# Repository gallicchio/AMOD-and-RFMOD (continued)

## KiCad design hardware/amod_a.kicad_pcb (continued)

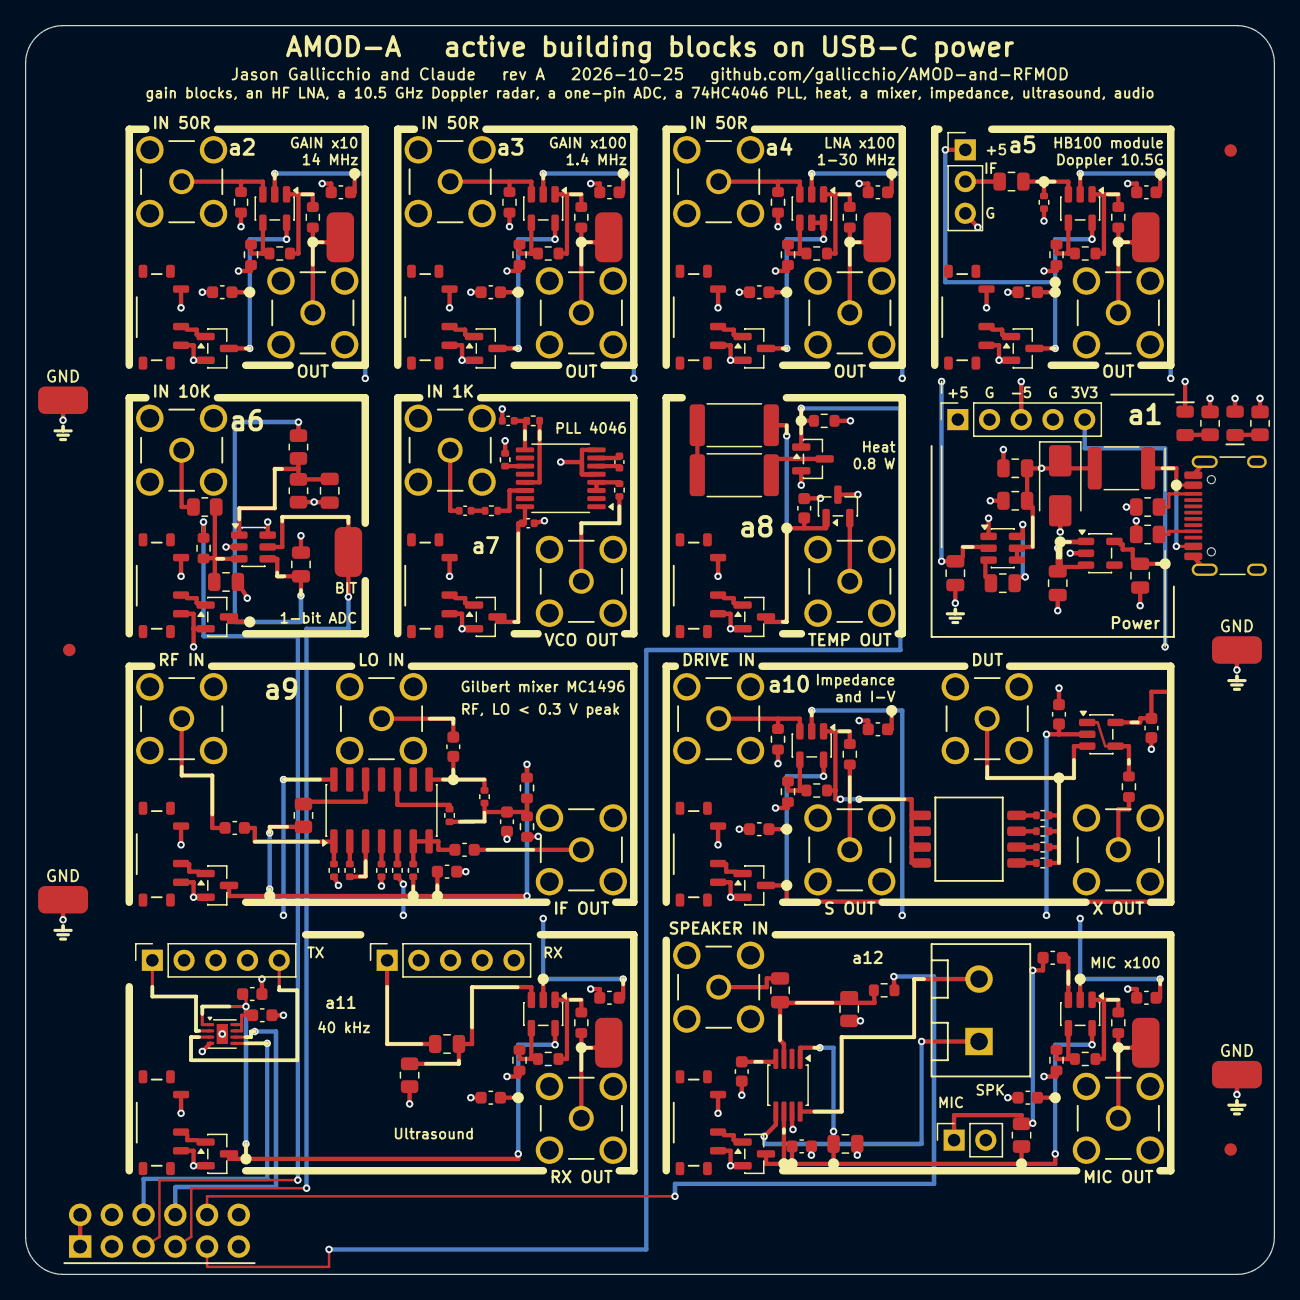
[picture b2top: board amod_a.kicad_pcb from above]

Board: 4 copper layers, 100.0 x 100.0 mm, 188 parts (0 on the bottom side), 114 nets.

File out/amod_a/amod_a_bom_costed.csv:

Comment,Designator,Footprint,LCSC Part #,MPN,Qty,Unit $,Ext $,JLC
1n,C703,C_0402_1005Metric,C1523,0402B102K500NT,1,0.0038,0.004,basic
100n,"C602,C603",C_0805_2012Metric,C49678,CC0805KRX7R9BB104,2,0.0205,0.041,basic
1u,"C1203,C1206",C_0603_1608Metric,C15849,CL10A105KB8NNNC,2,0.0146,0.029,basic
100n,"C701,C702,C704",C_0402_1005Metric,C1525,CL05B104KO5NNNC,3,0.0035,0.011,basic
10n,"C601,C1103,C1202",C_0805_2012Metric,C2971995,0805CG103J500NT,3,0.0421,0.126,extended
1u,"C105,C106,C501,C1201",C_0805_2012Metric,C28323,CL21B105KBFNNNE,4,0.0341,0.136,basic
10u,"C101,C102,C103,C104,C1205",C_0805_2012Metric,C15850,CL21A106KAYNNNE,5,0.0426,0.213,basic
100n,"C201,C202,C301,C302,C401,C402,C502,C503,C801,C901,C902,C903,C904,C905,C1001,C1002,C1003,C1004,C1101,C1102,C1104,C1105,C1204,C1207,C1208",C_0603_1608Metric,C14663,CC0603KRX7R9BB104,25,0.0084,0.210,basic
SMAJ5.0A,D101,D_SMA,C78401,SMAJ5.0A,1,0.0537,0.054,extended
2A,F101,Fuse_1812_4532Metric,C210837,MF-MSMF200-2,1,0.0650,0.065,extended
USB-C,J101,USB_C_Receptacle_HRO_TYPE-C-31-M-12,C165948,TYPE-C-31-M-12,1,0.1888,0.189,extended
rails,J102,PinSocket_1x05_P2.54mm_Vertical,C2894928,PZ254-1-05-Z-8.5,1,0.0588,0.059,extended
HB100,J502,PinHeader_1x03_P2.54mm_Vertical,C2937625,PZ254V-11-03P,1,0.0199,0.020,extended
TX,J1102,PinSocket_1x05_P2.54mm_Vertical,C2894928,PZ254-1-05-Z-8.5,1,0.0588,0.059,extended
RX,J1103,PinSocket_1x05_P2.54mm_Vertical,C2894928,PZ254-1-05-Z-8.5,1,0.0588,0.059,extended
Pmod,J1104,PinHeader_2x06_P2.54mm_Horizontal_PZ254R-12-12P,C492434,PZ254R-12-12P,1,0.1036,0.104,extended
SPK,J1203,TerminalBlock_KF301_1x02_P5.00mm,C474881,KF301-5.0-2P,1,0.1017,0.102,extended
MIC,J1204,PinSocket_1x02_P2.54mm_Vertical,C2894925,PZ254-1-02-Z-8.5,1,0.0266,0.027,extended
SMA,"J201,J202,J301,J302,J401,J402,J501,J601,J701,J702,J801,J901,J902,J903,J1001,J1002,J1003,J1004,J1101,J1201,J1202",SMA_BWSMA-KE-Z001_Vertical,C496549,BWSMA-KE-Z001,21,0.4043,8.490,extended
-5V,LED101,LED_0805_2012Metric_Kbar,C84256,NCD0805R1,1,0.0135,0.013,basic
+5V,LED102,LED_0805_2012Metric_Kbar,C2297,KT-0805G,1,0.0164,0.016,basic
AO3400A,Q802,SOT-23,C20917,AO3400A,1,0.0889,0.089,basic
AO3401A,"Q201,Q301,Q401,Q501,Q601,Q701,Q801,Q901,Q1001,Q1101,Q1201",SOT-23,C15127,AO3401A,11,0.0959,1.055,basic
1.1k,R204,R_0603_1608Metric,C22764,0603WAF1101T5E,1,0.0018,0.002,extended
10R,R404,R_0603_1608Metric,C22859,0603WAF100JT5E,1,0.0032,0.003,basic
100k,R501,R_0402_1005Metric,C25741,0402WGF1003TCE,1,0.0015,0.002,basic
3.9k,R904,R_0402_1005Metric,C51721,0402WGF3901TCE,1,0.0012,0.001,extended
1.5k,R905,R_0402_1005Metric,C25867,0402WGF1501TCE,1,0.0029,0.003,basic
1.5k,R906,R_0805_2012Metric,C4310,0805W8F1501T5E,1,0.0038,0.004,basic
47,R1005,R_0402_1005Metric,C25118,0402WGF470JTCE,1,0.0012,0.001,basic
4.7k,R1007,R_0402_1005Metric,C25900,0402WGF4701TCE,1,0.0021,0.002,basic
47k,R1008,R_0402_1005Metric,C25792,0402WGF4702TCE,1,0.0020,0.002,basic
3.9k,R1101,R_0805_2012Metric,C17614,0805W8F3901T5E,1,0.0030,0.003,basic
2.2k,R1202,R_0805_2012Metric,C17520,0805W8F2201T5E,1,0.0049,0.005,basic
5.1k,"R101,R102",R_0805_2012Metric,C27834,0805W8F5101T5E,2,0.0036,0.007,basic
1k,"R103,R104",R_0805_2012Metric,C17513,0805W8F1001T5E,2,0.0035,0.007,basic
1k,"R701,R902",R_0402_1005Metric,C11702,0402WGF1001TCE,2,0.0013,0.003,basic
10k,"R702,R703",R_0402_1005Metric,C25744,0402WGF1002TCE,2,0.0011,0.002,basic
15R,"R801,R802",R_2512_6332Metric,C20087,25121WF150JT4E,2,0.0375,0.075,extended
470,"R704,R1006",R_0402_1005Metric,C25117,0402WGF4700TCE,2,0.0012,0.002,basic
10k,"R601,R603,R604",R_0805_2012Metric,C17414,0805W8F1002T5E,3,0.0034,0.010,basic
1k,"R402,R1002,R1004",R_0603_1608Metric,C21190,0603WAF1001T5E,3,0.0017,0.005,basic
51,"R901,R903,R907,R908",R_0402_1005Metric,C25125,0402WGF510JTCE,4,0.0012,0.005,extended
100R,"R304,R504,R1104,R1205",R_0603_1608Metric,C22775,0603WAF1000T5E,4,0.0023,0.009,basic
10k,"R202,R302,R502,R602,R803,R909,R910,R1102,R1201,R1203",R_0603_1608Metric,C25804,0603WAF1002T5E,10,0.0022,0.022,basic
49.9,"R201,R203,R301,R303,R401,R403,R503,R1001,R1003,R1009,R1103,R1204",R_0603_1608Metric,C6230117,SR0603FR-7T49R9L,12,0.0150,0.180,extended
DIP4,SW1002,SW_DIP_SPSTx04_Slide_1.27mm_DSHP04,C40736,DSHP04TSGET,1,0.5450,0.545,extended
ON,"SW201,SW301,SW401,SW501,SW601,SW701,SW801,SW901,SW1001,SW1101,SW1201",SW_SPDT_Shouhan_MSK12C02,C431540,MSK12C02,11,0.0529,0.582,extended
BIT,TP601,TestPoint_Loop_RH-5019,C5199800,RH-5019,1,0.0966,0.097,extended
GND,"TP9901,TP9902,TP9903,TP9904",TestPoint_Loop_RH-5019,C5199800,RH-5019,4,0.0966,0.386,extended
OUT,"TP201,TP301,TP401,TP501,TP1101,TP1201",TestPoint_Loop_RH-5019,C5199800,RH-5019,6,0.0966,0.580,extended
LM2664,U101,SOT-23-6,C108573,LM2664M6X/NOPB,1,0.3346,0.335,extended
3.3V,U102,SOT-23-5,C2862740,TPS7A2033PDBVR,1,0.2097,0.210,extended
OPA847,U401,SOT-23-6,C2059024,OPA847IDBVT,1,9.5279,9.528,extended
TLV3501,U601,SOT-23-6,C193413,TLV3501AIDBVR,1,1.9246,1.925,extended
74HC4046A,U701,TSSOP-16_4.4x5mm_P0.65mm,C546981,74HC4046APW-Q100J,1,1.1816,1.182,extended
TMP235,U801,SOT-23,C2868809,TMP235A4DBZR,1,0.3243,0.324,extended
MC1496,U901,SOIC-14_3.9x8.7mm_P1.27mm,C7295,MC1496DR2G,1,0.2492,0.249,extended
DRV8837,U1101,Texas_DSG0008A_WSON-8-1EP_2x2mm_P0.5mm_EP0.9x1.6mm,C39159,DRV8837DSGR,1,0.2622,0.262,extended
PAM8302A,U1201,MSOP-8_3x3mm_P0.65mm,C113367,PAM8302AASCR,1,0.3089,0.309,extended
OPA810,"U201,U301,U501,U1001,U1002,U1102,U1202",SOT-23-5,C2833513,OPA810IDBVR,7,3.0996,21.697,extended
